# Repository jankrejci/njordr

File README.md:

# vetroplach-firmware

Firmware for an ultrasonic anemometer.

## Prerequisites

This project uses a `nix develop` environment, so you should have [Nix](https://nixos.org/download/#download-nix) installed on your computer.
Additionally, `probe-rs` is used for flashing and debugging.
Please ensure you have completed the [probe setup](https://probe.rs/docs/getting-started/probe-setup/#linux-udev-rules),
especially the udev rules if you're on Linux.

## Building

Enable the development environment:
```bash
nix develop
```

Build and run the project:
```bash
cargo run --release  
```

Or build and run an example:
```bash
cargo run --release --example pwm-source
```

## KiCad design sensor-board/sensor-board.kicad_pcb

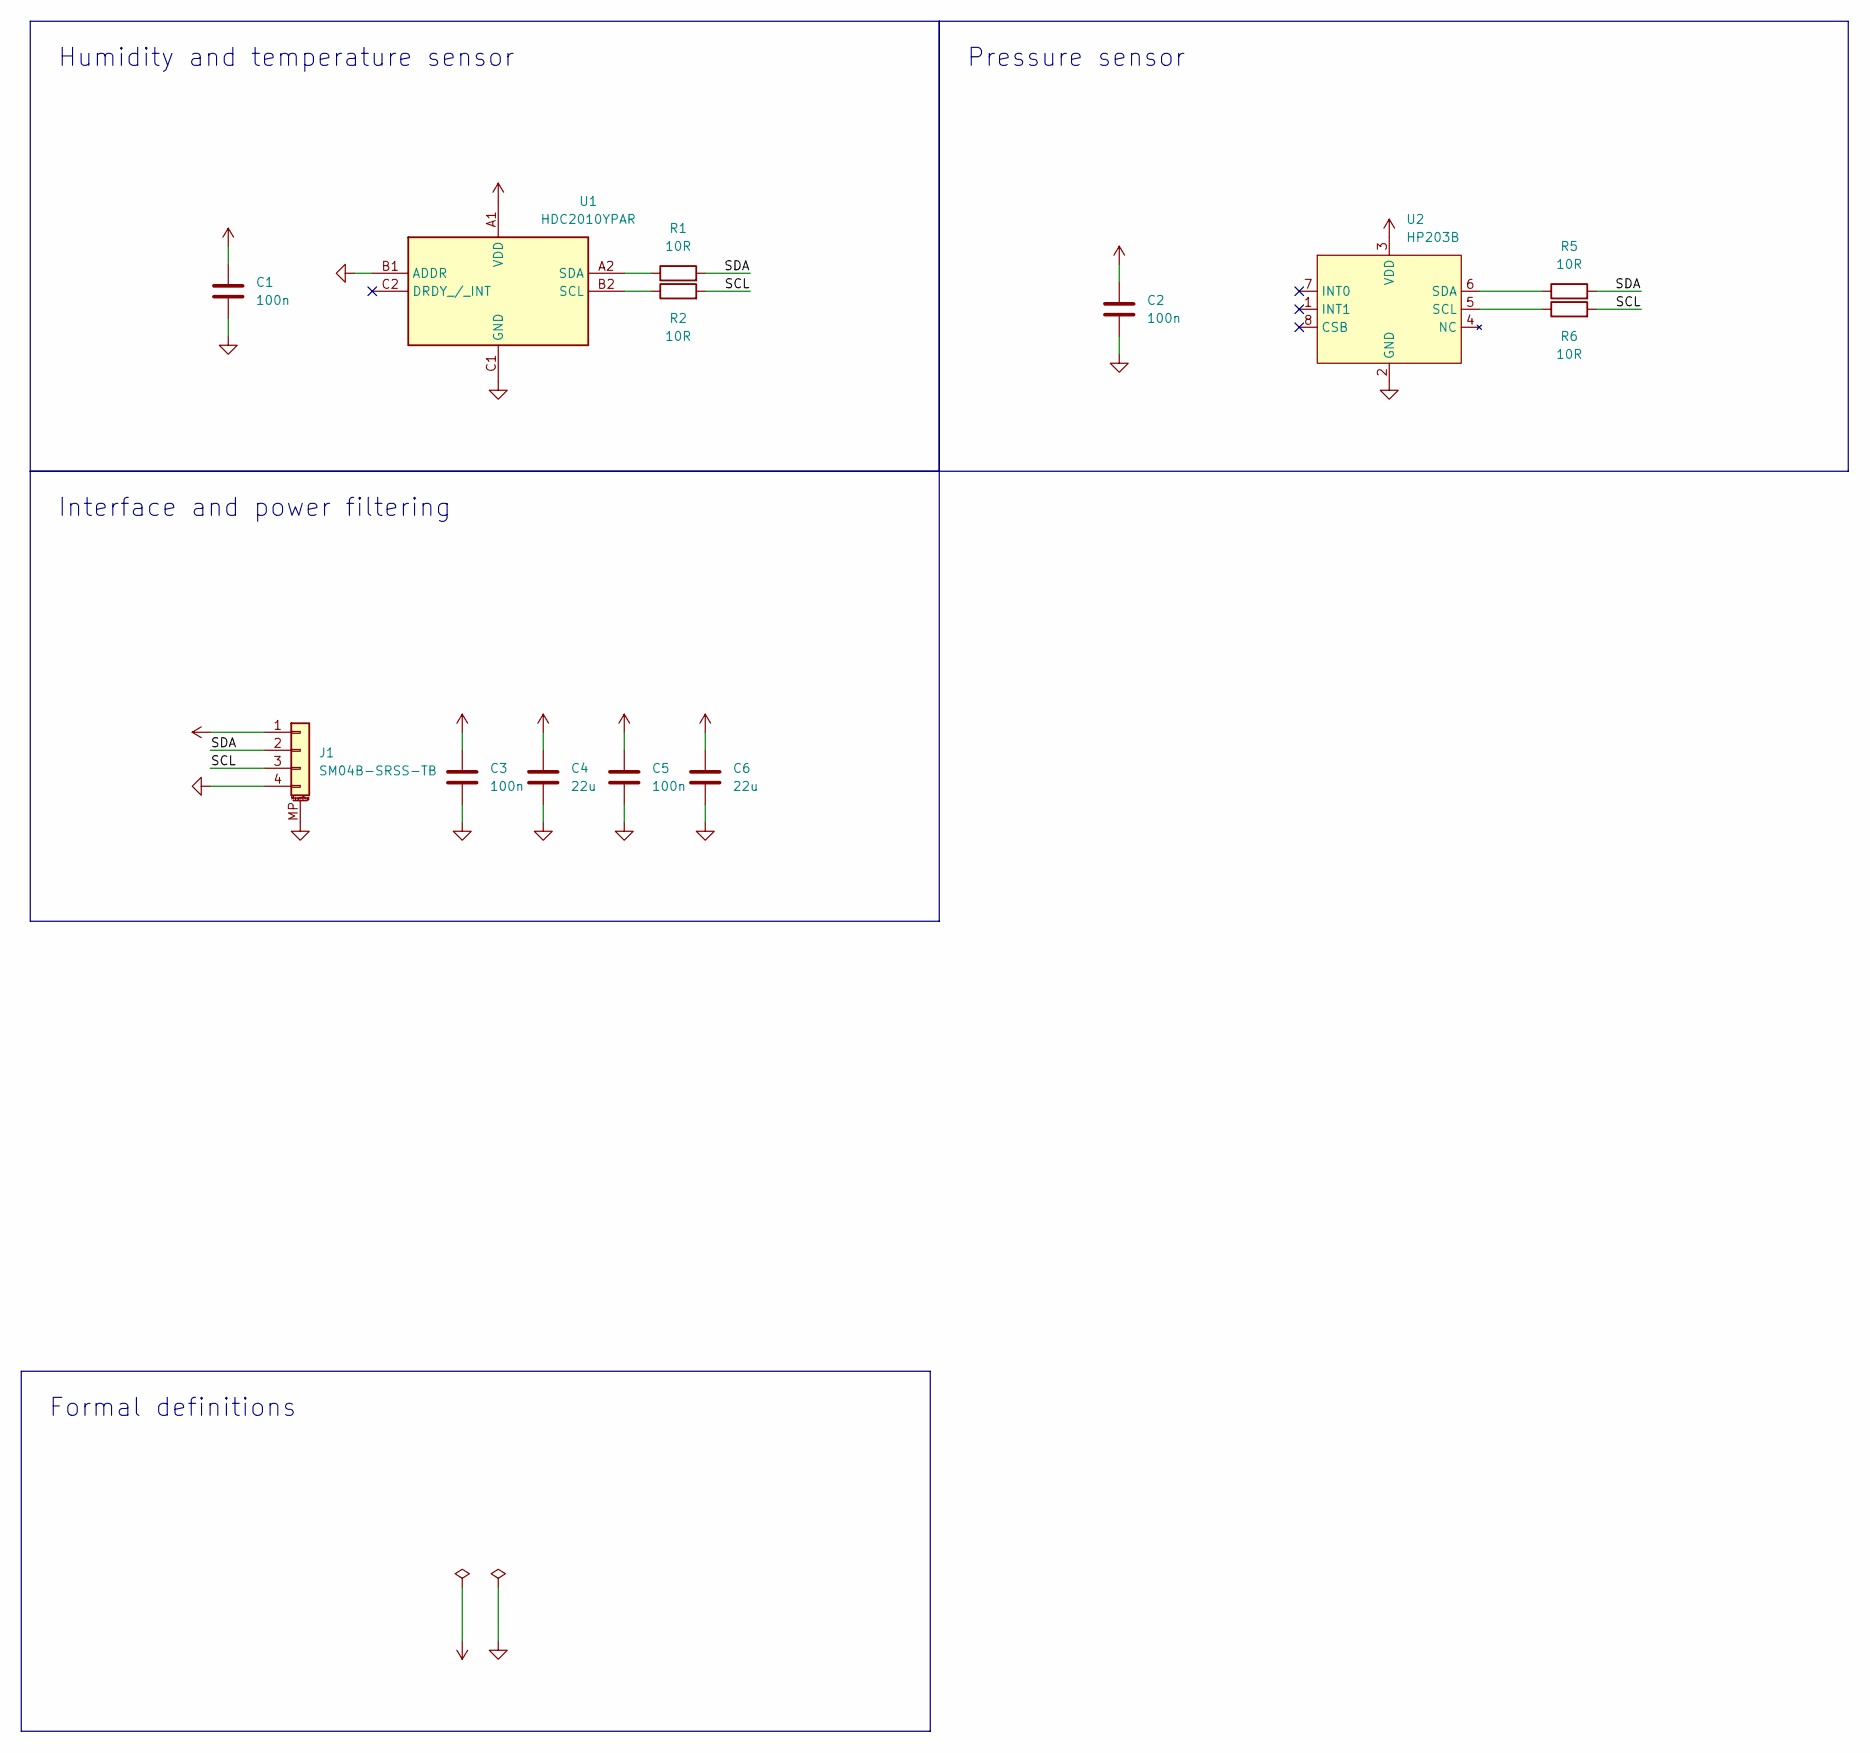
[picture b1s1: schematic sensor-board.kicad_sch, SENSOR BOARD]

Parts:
C1, C2, C3, C5: 100n; C-0603-HandSolder; LCSC C14663
C4, C6: 22u; C-0805-HandSolder; LCSC C59461
J1: SM04B-SRSS-TB; LCSC C160404
R1, R2, R5, R6: 10R; R-0603-HandSolder; LCSC C22859
U1: HDC2010YPAR; DSBGA-6-1.5x1.5; LCSC C477922
U2: HP203B; QFN-8-HP203B; LCSC C138665

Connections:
/SCL: J1.3, R2.2, R6.2
/SDA: J1.2, R1.2, R5.2
GND: C1.2, C2.2, C3.2, C4.2, C5.2, C6.2, J1.4, J1.MP (MountPin), U1.B1 (ADDR), U1.C1 (GND), U2.2 (GND)
unnamed: R2.1, U1.B2 (SCL)
unnamed: R1.1, U1.A2 (SDA)
unnamed: R6.1, U2.5 (SCL)
unnamed: R5.1, U2.6 (SDA)
VCC: C1.1, C2.1, C3.1, C4.1, C5.1, C6.1, J1.1, U1.A1 (VDD), U2.3 (VDD)

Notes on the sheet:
Interface and power filtering
Pressure sensor
Formal definitions
Humidity and temperature sensor

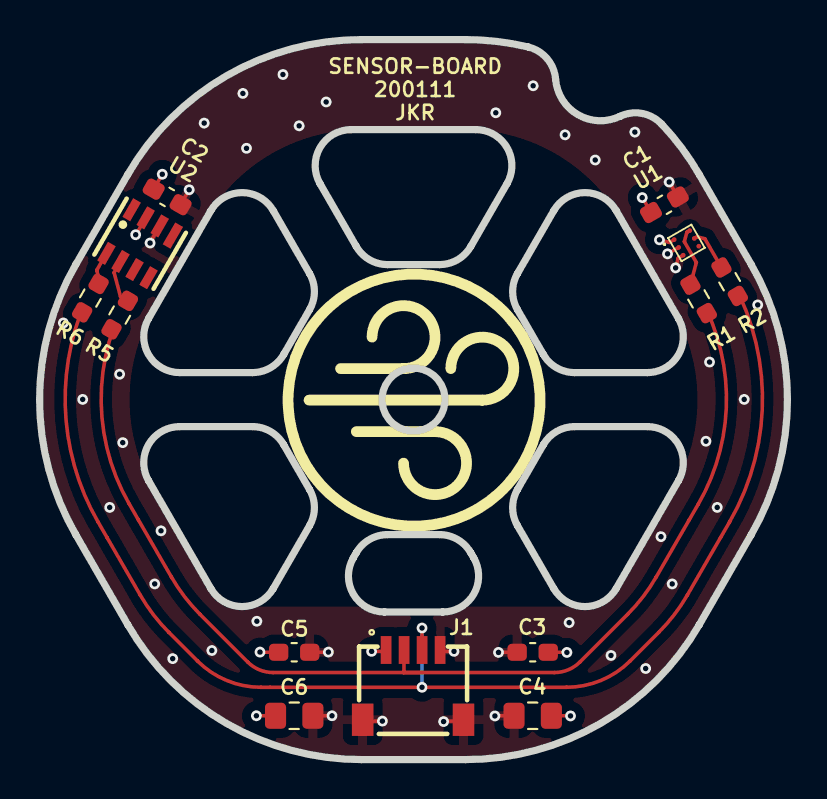
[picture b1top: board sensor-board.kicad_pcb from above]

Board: 4 copper layers, 41.5 x 40.0 mm, 13 parts (0 on the bottom side), 8 nets.

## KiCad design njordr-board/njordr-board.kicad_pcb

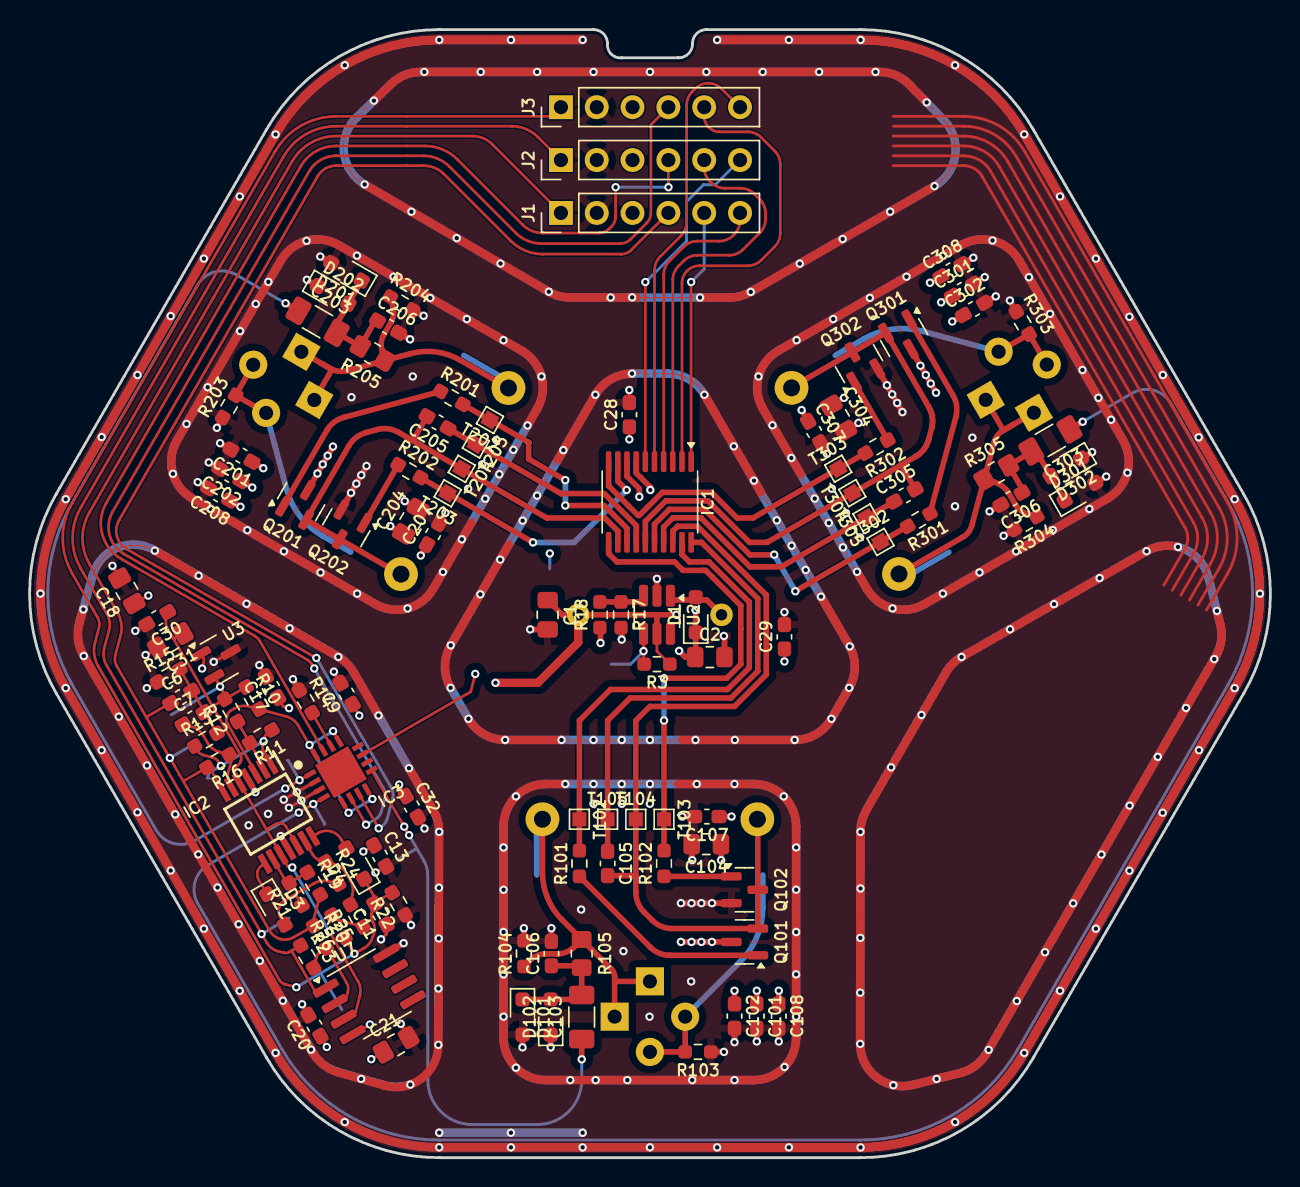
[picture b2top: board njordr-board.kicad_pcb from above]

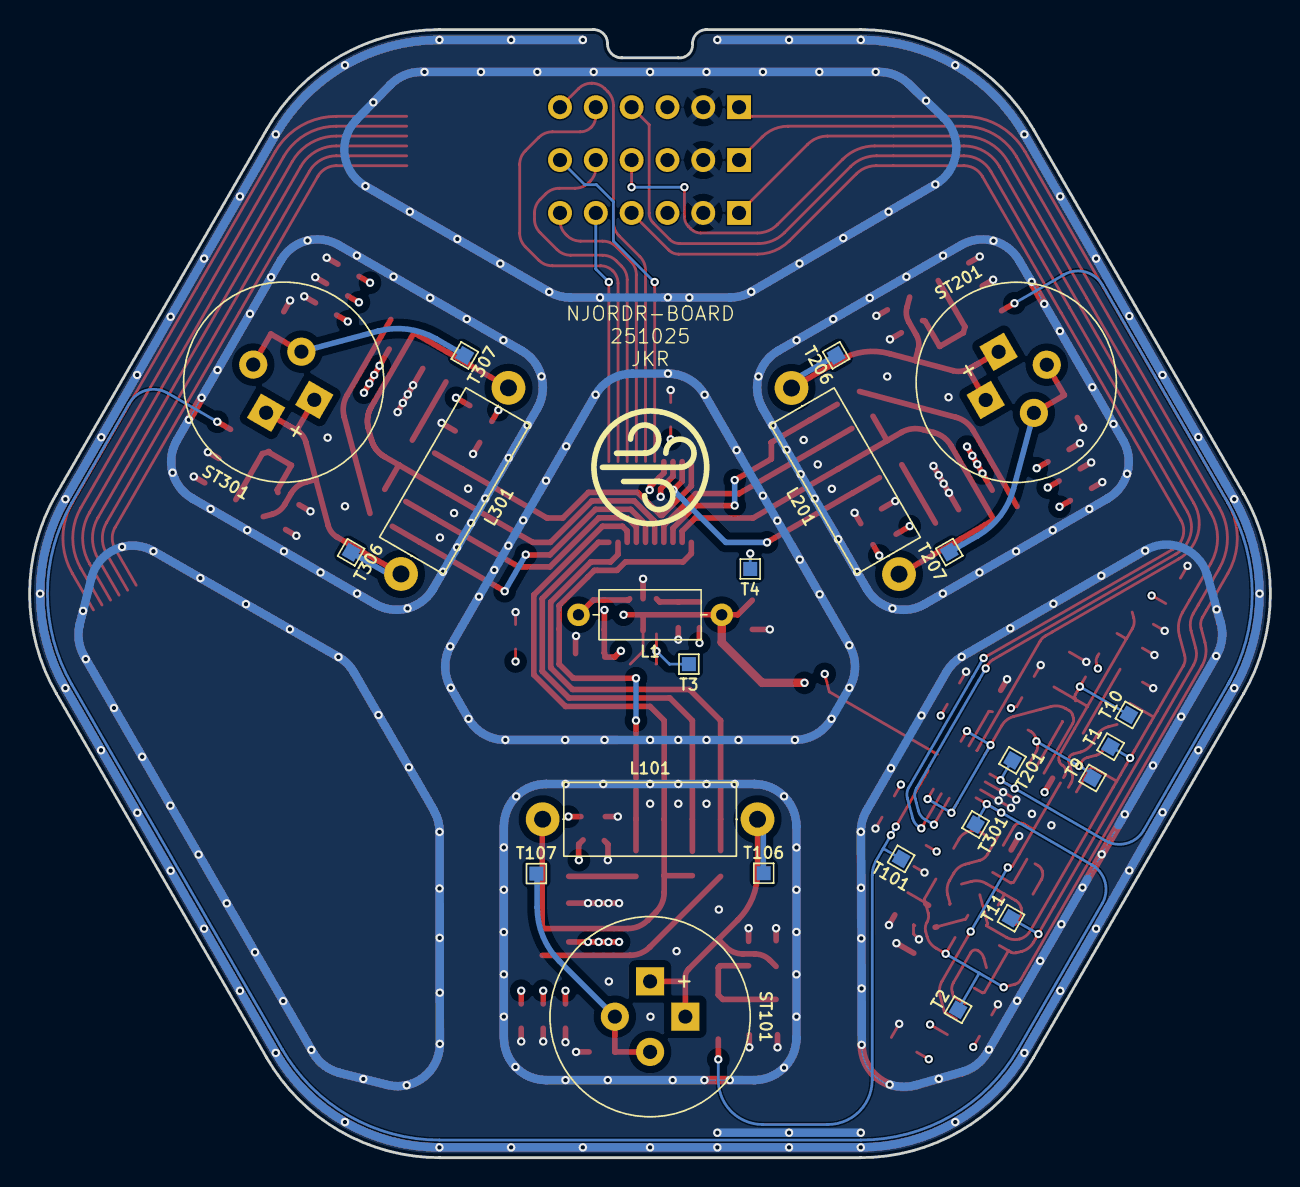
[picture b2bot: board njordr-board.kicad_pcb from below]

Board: 4 copper layers, 88.0 x 80.0 mm, 132 parts (23 on the bottom side), 62 nets.

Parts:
C1, C2, C18, C21, C31, C104, C204, C304: 22u; C-0805-HandSolder
C6, C106, C206, C306: 330p; C-0603-HandSolder
C7: 220p; C-0603-HandSolder
C9, C11, C13, C17, C20, C28, C29, C30, C32, C101, C105, C107, C108, C201, C205, C207, C208, C301, C305, C307, C308: 100n; C-0603-HandSolder
C102, C202, C302: 1u; C-0603-HandSolder
C103, C203, C303: 1n; C-1206-HandSolder
D1: 1N5819WS; D-SOD-323-HandSolder
D3, D4, D101, D102, D201, D202, D301, D302: 1N4148WS; D-SOD-323-HandSolder
IC1: DRV8300DPWR; TSSOP-20-4.4x6.5
IC2: GS8054; TSSOP-14-4.4x5.0
IC3: TMUX741x; WQFN-16-4.0x4.0
J1, J2, J3: Conn_01x06; PinHeader-1x06-P2.54mm-Vertical
L1: 6u8; L-Axial-L7.0-D3.3mm-P10.16
L101, L201, L301: 8.2mH; L-Axial-L12.0-D5.0-P15.24
Q101, Q102, Q201, Q202, Q301, Q302: 2N7002; SOT-23
R3, R12, R14, R17, R20: 10k; R-0603-HandSolder
R10, R11, R23: 100k; R-0603-HandSolder
R13, R104, R204, R304: 2k2; R-0603-HandSolder
R15: 4k7; R-0603-HandSolder
R16: 150k; R-0603-HandSolder
R18: 330k; R-0603-HandSolder
R19: 2k; R-0603-HandSolder
R21, R22: 1k; R-0603-HandSolder
R24, R25, R26: 3k; R-0603-HandSolder
R101, R102, R103, R201, R202, R203, R301, R302, R303: 10R; R-0603-HandSolder
R105, R205, R305: 0R; R-0805-HandSolder
ST101, ST201, ST301: Speaker_Ultrasound; CUSA-TR65-065-2200-TH68
T1, T2, T3, T4, T9, T10, T11, T101, T102, T103, T104, T105, T106, T107, T201, T202, T203, T204, T205, T206, T207, T301, T302, T303, T304, T305, T306, T307: TestPoint; TestPoint-Pad-1.0x1.0
U2: MT3608; SOT-23-6-HandSolder
U3: REF3012; SOT-23
U7: LM393; SOIC-8-3.9x4.9-P1.27

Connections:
+3.3V: C1.1, C9.1, C13.1, C17.1, C18.1, C20.1, C21.1, C32.1, IC2.4 (V+), J1.3, J2.3, J3.3, L1.1, R3.1, U2.5 (IN), U3.1 (IN), U7.4 (V-)
+24V: C2.1, C28.1, C29.1, C101.1, C102.1, C104.1, C107.1, C108.1, C201.1, C202.1, C204.1, C207.1, C208.1, C301.1, C302.1, C304.1, C307.1, C308.1, D1.1 (K), IC1.7 (GVDD), IC3.11 (VDD), Q101.3 (D), Q201.3 (D), Q301.3 (D), R18.1, T4.1
/ECHO: C6.1, IC2.7, J1.1, R16.2, R19.2, R20.1, T1.1
/EDGE: J2.1, R23.1, T11.1, U7.1
/ENVELOPE: C11.2, D4.1 (K), J3.1, R22.2, R26.1, T2.1
/RX_EN_CH1: IC3.7 (SEL3), J1.4
/RX_EN_CH2: IC3.15 (SEL1), J2.4
/RX_EN_CH3: IC3.6 (SEL4), J3.4
/interface/BOOTSTRAP_CH1: C105.1, IC1.20 (BSTA), T105.1
/interface/BOOTSTRAP_CH2: C205.1, IC1.14 (BSTC), T205.1
/interface/BOOTSTRAP_CH3: C305.1, IC1.17 (BSTB), T305.1
/interface/GATE_HIGH_CH1: IC1.19 (GHA), R101.2, T102.1
/interface/GATE_HIGH_CH2: IC1.13 (GHC), R201.2, T202.1
/interface/GATE_HIGH_CH3: IC1.16 (GHB), R301.2, T302.1
/interface/GATE_LOW_CH1: IC1.11 (GLA), R102.2, T103.1
/interface/GATE_LOW_CH2: IC1.9 (GLC), R202.2, T203.1
/interface/GATE_LOW_CH3: IC1.10 (GLB), R302.2, T303.1
/interface/INPUT_HIGH_CH1: IC1.1 (INHA), J1.5
/interface/INPUT_HIGH_CH2: IC1.3 (INHC), J2.5
/interface/INPUT_HIGH_CH3: IC1.2 (INHB), J3.5
/interface/INPUT_LOW_CH1: IC1.4 (INLA), J1.6
/interface/INPUT_LOW_CH2: IC1.6 (INLC), J2.6
/interface/INPUT_LOW_CH3: IC1.5 (INLB), J3.6
/interface/SENSE_CH1: C105.2, IC1.18 (SHA), L101.1, Q101.2 (S), Q102.3 (D), T104.1
/interface/SENSE_CH2: C205.2, IC1.12 (SHC), L201.1, Q201.2 (S), Q202.3 (D), T204.1
/interface/SENSE_CH3: C305.2, IC1.15 (SHB), L301.1, Q301.2 (S), Q302.3 (D), T304.1
/interface/~BOOSTER_EN: R3.2, T3.1, U2.4 (EN)
/signal-priming/ECHO_CH1: C103.1, IC3.9 (S3), T101.1
/signal-priming/ECHO_CH2: C203.1, IC3.1 (S1), T201.1
/signal-priming/ECHO_CH3: C303.1, IC3.4 (S4), T301.1
/signal-priming/ECHO_IN: IC2.3 (+), IC3.5 (D4), IC3.8 (D3), IC3.13 (D2), IC3.16 (D1), R10.2
/signal-priming/STAGE_A: IC2.1, R11.1, R13.1, T9.1
/signal-priming/VREF: C30.1, C31.1, IC2.5 (+), IC2.10 (+), IC2.12 (+), R10.1, R12.2, T10.1, U3.2 (OUT), U7.3 (+)
/sonic-ch1/SONIC: L101.2, R104.1, R105.1, ST101.1, T106.1
/sonic-ch2/SONIC: L201.2, R204.1, R205.1, ST201.1, T206.1
/sonic-ch3/SONIC: L301.2, R304.1, R305.1, ST301.1, T306.1
GND: C1.2, C2.2, C9.2, C11.1, C13.2, C17.2, C18.2, C20.2, C21.2, C28.2, C29.2, C30.2, C31.2, C32.2, C101.2, C102.2, C104.2, C106.2, C107.2, C108.2, C201.2, C202.2, C204.2, C206.2, C207.2, C208.2, C301.2, C302.2, C304.2, C306.2, C307.2, C308.2, D101.2 (A), D102.1 (K), D201.2 (A), D202.1 (K), D301.2 (A), D302.1 (K), IC1.8 (GND), IC2.11 (V-), IC3.2 (VSS), IC3.3 (GND), J1.2, J2.2, J3.2, Q102.2 (S), Q202.2 (S), Q302.2 (S), R14.1, R15.1, R17.2, R22.1, R103.1, R104.2, R203.1, R204.2, R303.1, R304.2, U2.2 (GND), U3.3 (GND), U7.8 (V+)
unnamed: C6.2, C7.2, R13.2, R15.2
unnamed: D1.2 (A), L1.2, U2.1 (SW)
unnamed: D3.2 (A), R21.1, R24.2
unnamed: D3.1 (K), IC2.8
unnamed: D4.2 (A), IC2.14
unnamed: C103.2, C106.1, D101.1 (K), D102.2 (A), R105.2
unnamed: C203.2, C206.1, D201.1 (K), D202.2 (A), R205.2
unnamed: C303.2, C306.1, D301.1 (K), D302.2 (A), R305.2
unnamed: IC2.2 (-), R11.2, R12.1
unnamed: C7.1, IC2.6 (-), R16.1
unnamed: IC2.9 (-), R19.1, R21.2
unnamed: IC2.13 (-), R24.1, R25.2
unnamed: IC3.14 (SEL2), R14.2
unnamed: Q101.1 (G), R101.1
unnamed: Q102.1 (G), R102.1
unnamed: Q201.1 (G), R201.1
unnamed: Q202.1 (G), R202.1
unnamed: Q301.1 (G), R301.1
unnamed: Q302.1 (G), R302.1
unnamed: R25.1, R26.2
unnamed: R103.2, ST101.2, T107.1
unnamed: R203.2, ST201.2, T207.1
unnamed: R303.2, ST301.2, T307.1
unnamed: R17.1, R18.2, U2.3 (FB)
unnamed: R20.2, R23.2, U7.2 (-)

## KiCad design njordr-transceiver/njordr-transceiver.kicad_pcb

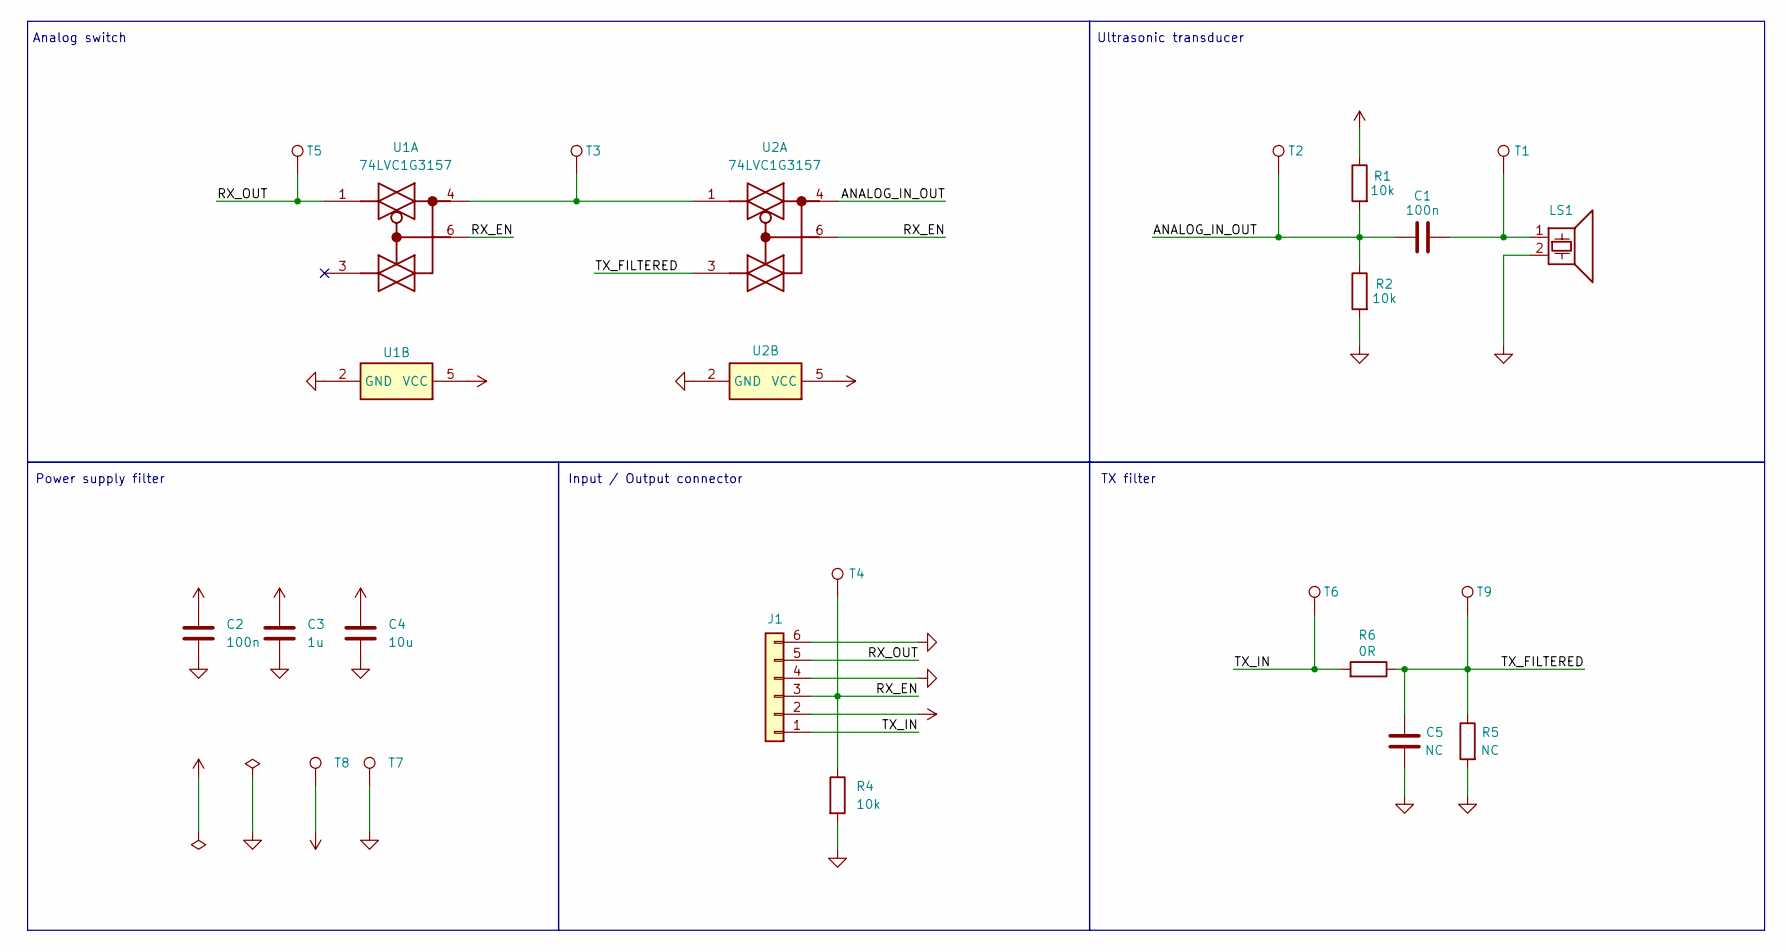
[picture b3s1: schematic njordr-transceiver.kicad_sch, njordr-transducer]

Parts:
C1, C2: 100n; C_0603_1608Metric_Pad1.08x0.95mm_HandSolder; LCSC C14663
C3: 1u; C_0603_1608Metric_Pad1.08x0.95mm_HandSolder; LCSC C15849
C4: 10u; C_0603_1608Metric_Pad1.08x0.95mm_HandSolder; LCSC C19702
C5: NC; C_0603_1608Metric_Pad1.08x0.95mm_HandSolder
J1: Conn_01x06; PinHeader_1x06_P2.54mm_Vertical
LS1: Speaker_Ultrasound; Buzzer_D14mm_H7mm_P10mm
R1, R2, R4: 10k; R_0603_1608Metric_Pad0.98x0.95mm_HandSolder; LCSC C25804
R5: NC; R_0603_1608Metric_Pad0.98x0.95mm_HandSolder
R6: 0R; R_0603_1608Metric_Pad0.98x0.95mm_HandSolder; LCSC C21189
T1, T2, T3, T4, T5, T6, T9: TestPoint; TestPoint_THTPad_1.0x1.0mm_Drill0.5mm
T7, T8: TestPoint; TestPoint_THTPad_2.0x2.0mm_Drill1.0mm
U1, U2: 74LVC1G3157; SOT-363_SC-70-6_Handsoldering; LCSC C38663

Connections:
+3.3V: C2.1, C3.1, C4.1, J1.2, R1.1, T8.1, U1.5 (VCC), U2.5 (VCC)
/ANALOG_IN_OUT: C1.2, R1.2, R2.1, T2.1, U2.4
/RX_EN: J1.3, R4.1, T4.1, U1.6, U2.6
/RX_OUT: J1.5, T5.1, U1.1
/TX_FILTERED: C5.2, R5.1, R6.1, T9.1, U2.3
/TX_IN: J1.1, R6.2, T6.1
GND: C2.2, C3.2, C4.2, C5.1, J1.4, J1.6, LS1.2, R2.2, R4.2, R5.2, T7.1, U1.2 (GND), U2.2 (GND)
unnamed: C1.1, LS1.1, T1.1
unnamed: T3.1, U1.4, U2.1

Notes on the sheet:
Analog switch
TX filter
Ultrasonic transducer
Power supply filter
Input / Output connector

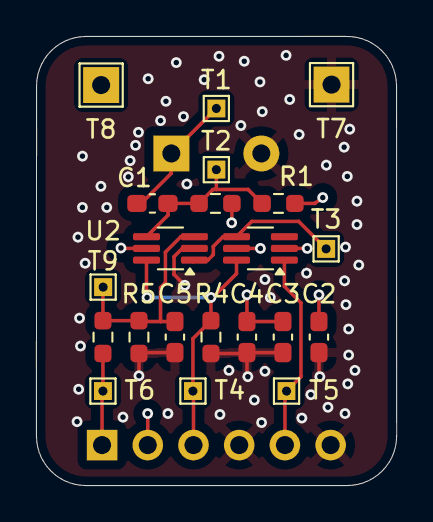
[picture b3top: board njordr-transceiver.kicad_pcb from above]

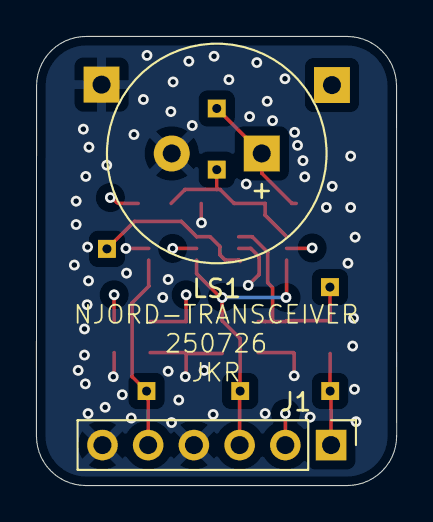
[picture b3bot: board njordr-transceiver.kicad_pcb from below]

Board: 4 copper layers, 20.0 x 25.0 mm, 23 parts (2 on the bottom side), 9 nets.

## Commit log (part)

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2025-07-21 Introduce the flake.nix for development environment setup
    - invoke `nix develop` to configure complete toolchain
2025-07-21 Add gitignore to avoid unnecessary files
2025-07-22 Add flake.lock to pin packages
2025-07-22 Add support for the Helix editor
2025-07-22 Add simple example based on esp-generate template
    - use embassy as a runtime
    - use defmt for logging
    - use probe-rs for flashing / debugging
2025-07-22 Add basic PWM burst generator
    - modify the hello world example to be usable as a simple generator
    for analog circuitry testing
2025-07-22 Add basic github pipeline
2025-07-22 Add support for VScode editor
2025-07-22 Add Cargo.lock to pin crate versions
2025-07-27 firmware: Introduce examples
    - add examples folder and copy the pwm example there, this is more
    convenient for development
2025-07-27 firmware: Add basic instructions how to run the project
2025-07-27 firmware: Update the flake to be working also for NixOS system
    - toolchain installed via espup rely on shared libraries to be
    achievable on expected path, which is not the case in NixOS,
    so there is need to patch binaries to work properly
2025-07-27 firmware: Pin xtensa toolchain versions
    - avoid discrepancies between CI and local build system
2025-07-27 firmware: Move all the firmware related files into subfolder
    - there will be multiple components including kicad board files
    so keep it organized
2025-07-27 firmware: Introduce the flake.nix for development environment setup
    - invoke `nix develop` to configure complete toolchain
2025-07-27 firmware: Add gitignore to avoid unnecessary files
2025-07-27 firmware: Add flake.lock to pin packages
2025-07-27 firmware: Add simple example based on esp-generate template
    - use embassy as a runtime
    - use defmt for logging
    - use probe-rs for flashing / debugging
2025-07-27 firmware: Add Cargo.lock to pin crate versions
2025-07-27 firmware: Add support for the Helix editor
2025-07-27 firmware: Add support for VScode editor
2025-07-27 firmware: Add basic PWM burst generator
    - modify the hello world example to be usable as a simple generator
    for analog circuitry testing
2025-07-27 firmware: Add basic github pipeline
2025-07-27 transceiver: Add empty kicad project for njordr-transceiver
    - ignore all temporary files
2025-07-27 transceiver: Add transceiver circuitry and board
    - create a board for testing of the analog switches
2025-07-27 transceiver: Add gerber generating github pipeline
2025-07-27 firmware: Improve the firmware CI and remove duplicate checks
    - rename CI file to match folder naming
2025-10-25 firmware: Introduce the sonic module
    - introduce the claude software engineer agent
    - refactor the flake to be working on nixos as well on other distros
    - use the RMT peripheral to handle pulse generator
    - introduce the sonic module to handle the ultrasonic transducer
    - add frequency change support
2025-10-25 board: Create a board with all components integrated
    - move the transceiver folder to njordr-board, sensors will be assembled
    directly on the main board
    - implement the sonic driver
    - add the interface sheet
    - add simulation experiments
    - use mosfet gate driver for signal generator
2025-10-25 docs: Improve the board documentation
    - introduce script for component price evaluation
    - add basic driver and input filter simulations
    - describe the piezo driver
    - add DRV8300 sonic driver variant
2025-10-25 board: Improve board markings
    - rotate reference labels
    - add connector description
    - add logo
2025-10-25 board: Use lower resistor values for the envelope detector
    - try to lower impedance to have higher stability
2025-10-31 sensor-board: Introduce sensor board
    - create new folder for the subproject
    - create initial kicad project
    - add required components into the share library
    - cleanup the library
2025-10-31 sensor-board: Create basic PCB layout
2025-10-31 njordr-board: Use updated library symbols and packages
2025-10-31 docs: Improve sonic driver documentation
2025-10-31 sensor-board: Add dedicated github workflow for generating gerbers
2025-10-31 njordr-board: Update github workflow naming
2025-11-01 sensor-board: Finalize the first iteration
